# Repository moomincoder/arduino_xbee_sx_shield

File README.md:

# arduino_xbee_sx_shield
Arudino shield to mount an XBee SX module to

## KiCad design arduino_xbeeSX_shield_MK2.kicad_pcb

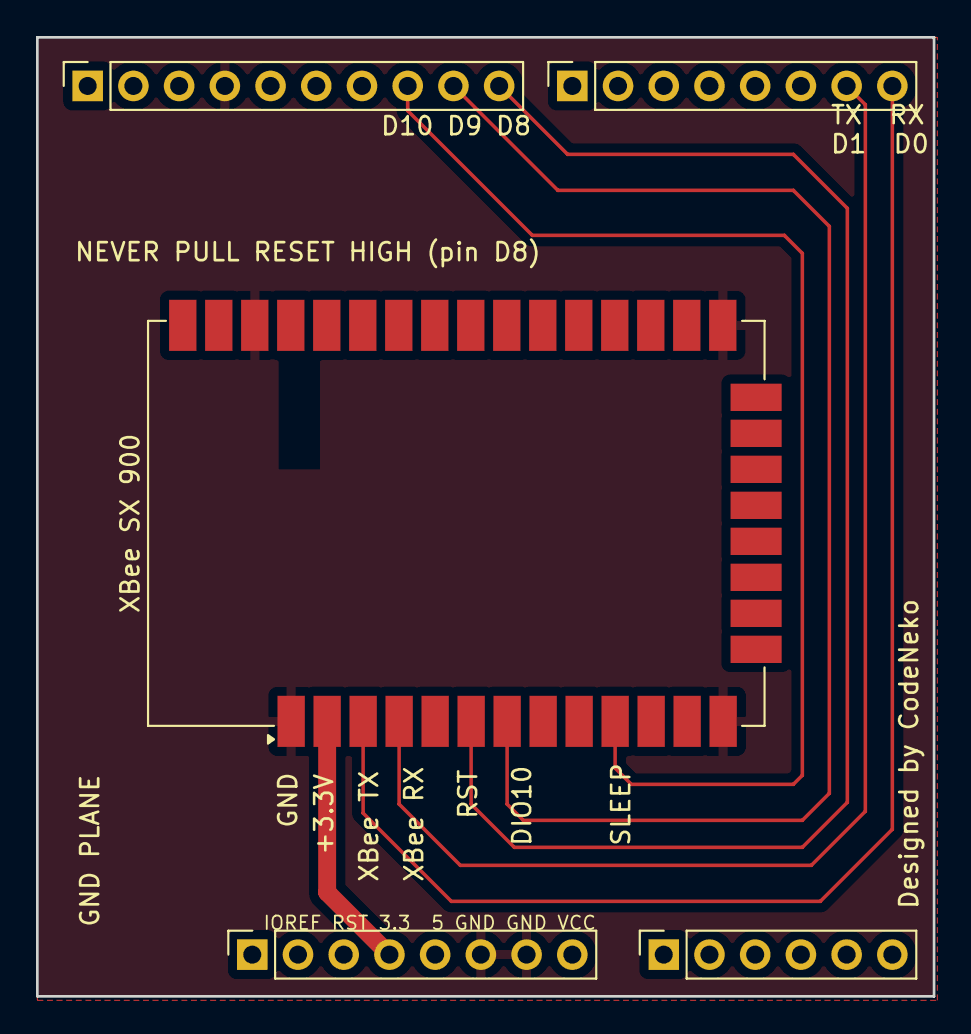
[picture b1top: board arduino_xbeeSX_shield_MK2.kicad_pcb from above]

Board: 2 copper layers, 49.8 x 53.3 mm, 5 parts (0 on the bottom side), 9 nets.

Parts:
J1: Power; PinSocket_1x08_P2.54mm_Vertical
J2: Digital/PWM; PinSocket_1x10_P2.54mm_Vertical
J3: Analog; PinSocket_1x06_P2.54mm_Vertical
J4: Digital/PWM; PinSocket_1x08_P2.54mm_Vertical
XBee SX 900: Digi_XBee_SMT

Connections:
+3V3: J1.4, XBee SX 900.2
/8: J2.10, XBee SX 900.6
/*9: J2.9, XBee SX 900.7
/*10: J2.8, XBee SX 900.10
/RX/0: J4.8, XBee SX 900.3
/SCL/A5: J2.1, J3.6
/SDA/A4: J2.2, J3.5
/TX/1: J4.7, XBee SX 900.4
GND: J1.6, J1.7, J2.4, XBee SX 900.1, XBee SX 900.13, XBee SX 900.22, XBee SX 900.35

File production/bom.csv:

Designator,Footprint,Quantity,Value,LCSC Part #
J1,PinSocket_1x08_P2.54mm_Vertical,1,Power,
J2,PinSocket_1x10_P2.54mm_Vertical,1,Digital/PWM,
J3,PinSocket_1x06_P2.54mm_Vertical,1,Analog,
J4,PinSocket_1x08_P2.54mm_Vertical,1,Digital/PWM,
XBEE SX 900,Digi_XBee_SMT,1,Digi_XBee_SMT,

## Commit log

2025-03-13 Adding the project
